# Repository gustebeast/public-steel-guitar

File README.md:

# Public Steel Guitar

A pedal steel guitar **you can build yourself, from parts anyone can buy.**

That is the whole point, and it is what the name means.

A pedal steel is a remarkable piece of engineering. The mechanical changer —
rods, bellcranks and pull-fingers moving a dozen strings through precise
intervals under hundreds of newtons, with a feel that generations of players
have refined — is one of the most sophisticated mechanisms in any instrument,
and the builders who make them are doing precision machining in small numbers,
by hand, at prices that reflect exactly that. It is skilled work and it is worth
what it costs.

It is also, by its nature, work that a player cannot do at home. That is the
constraint this project takes on: **not to make a better pedal steel, but to
make one that a person can source, build, modify and repair entirely
themselves.** Every printed part is in this repository as parametric source.
Every purchased part is a catalogue SKU with a supplier link in
[`BOM.md`](BOM.md), which comes to **~$1,060 per instrument** — approximate, and
several lines are still unverified — and the electronics are generated from
source too, so the boards can be re-fabbed by anyone rather than bought from us.
Motors dominate that total; there is one model, fully populated, with no
cut-down version. Nothing here needs a machine shop, a
proprietary part, or our involvement.

**Status:** CAD and electronics in progress; no physical prototype yet. The
mechanism is build-verified geometry (every commit is gated for part collisions,
swept collisions, wall thickness and unsupported overhangs), and **ten custom
PCBs are generated, routed and fab-packaged from source** — see `elec/`. What
does not exist yet is firmware: the copedent lives in a data table the 3D viewer
reads, and nothing commands a motor. [`docs/design-validation.md`](docs/design-validation.md)
tracks what the instrument can and cannot yet be shown to do, behaviour by
behaviour, including the open items. See
[`electromechanical-pedal-steel-spec.md`](electromechanical-pedal-steel-spec.md)
for the full design rationale and history.

**View it in 3D** (no install, no account):
<https://gustebeast.github.io/public-steel-guitar/> — an interactive model of the
instrument body, strings, nut block, and motor/changer drivetrain.

**License:** [CERN-OHL-S 2.0](LICENSE) (strongly reciprocal open hardware).

## Why it is built this way

Almost every design decision here follows from that one constraint. The
mechanism is not the goal; it is what is left once you insist that a person with
a 3D printer and a credit card can make the whole instrument. The column on the
left is not a criticism — it is the toolset a professional shop has and a player
usually does not.

| A shop can | So instead | Because |
|---|---|---|
| Mill a body from hardwood | **Printed PETG-GF and PCTG** | A printer is a machine people already own, and a file is not tooling. Changing a dimension is an edit, not a new setup. |
| Machine a changer: rods, bellcranks, pull-fingers, fitted as a set | **One commodity stepper and a GT2 belt per string** | Nothing in the drivetrain is made to order. A stepper, a belt, a trapezoidal screw and a nut are catalogue parts with several suppliers each. |
| Set the copedent in the pull-rod geometry | **The copedent is a data table** | Falls out of the above rather than being the aim: once each string has its own actuator, the mapping is software and costs nothing to change. |
| Keep spares and service what it built | **Every part is a file or a SKU** | Print the part again, or order the same screw — without depending on any one supplier staying in business. |
| Ream, tap, press and fit by hand | **One 2.5 mm hex key, heat-set inserts, no glue** | Fewest tools, one screw family, and every joint comes apart — so it can be repaired and modified, not just built. |

**What this gives up is real.** A mechanical steel needs no electricity, no
firmware and no motors; it will work in fifty years with a screwdriver, and its
feel is the product of decades of refinement by people who play them. This
instrument trades all of that for self-sufficiency. It is a different
instrument, not a cheaper copy of a good one — and if you want a pedal steel
rather than this, buy one from a builder.

## The concept, in one paragraph

So: each of the 10 strings terminates on the **nut of its own self-locking
leadscrew**, driven by a **closed-loop stepper** (MKS SERVO42D) through a
twisted GT2 belt. A traditional pedal steel changes pitch by pulling the
string's anchor with a mechanical changer, and which pedal pulls which string is
fixed in the hardware; giving every string its own stock actuator is the
cheapest way to get the same job done out of parts that already exist.
Pedals and levers are just **sensors**; firmware looks up the active copedent
and commands the relevant motors to new positions. Any pedal can bend any
combination of strings by any interval, changeable between songs. Because the
fine-pitch single-start screw is **non-back-drivable**, string tension cannot
move it: the motors are completely unpowered at rest — no holding current, no
heat, no idle noise — and the instrument holds its tuning even switched off.

## System concepts

Everything below is downstream of the buildability constraint: where there was a
choice between a clever part and an obtainable one, the obtainable one won.

- Per-string servo/stepper actuation of a pedal-steel changer, with a
  **software-reconfigurable copedent** (pedal/lever sensors → lookup →
  per-string position targets).
- **One bearing size, one screw family, one hex key.** A 688ZZ carries every
  axle; every fastener is an M4 button head on a 2.5 mm key; threads are
  heat-set brass inserts rather than tapped plastic. Fewer SKUs to source is
  the same goal as fewer tools to own.
- **No glue and no flex fittings anywhere.** Every joint is a screw, a slide or
  a captured pin, so any part can come out and be reprinted — which is what
  makes a repair a repair rather than a rebuild.
- A **self-locking (non-back-drivable) leadscrew per string** holding pitch
  with zero motor power, and serving as the tuning machine (no manual tuners).
- **Two nested control loops**: a fast feed-forward path (pedal position →
  copedent → motor position) with no pitch detection in the playing path, and
  a slow calibration loop using per-string pickup **pitch detection to correct
  the position→pitch map** (drift correction without touching the copedent).
- A **CAN-bus network of closed-loop actuators** (one node per string)
  commanded by a central controller reading pedal/lever angle sensors.
- The **vertical under-string actuator layout**: each string turns 90° over a
  per-string bridge bearing and runs down to a short vertical screw, motors
  lying flat under the speaking length in a staircase, driven by twisted
  belts — yielding a thin instrument (~100 mm).
- String termination is a **laser-cut steel nut plate** per string: its
  crown is the break, the string takes ONE wrap round a shared Ø8 rod, the
  plate's shelf pinches the one strand under the rod, and a side screw pins
  the tail to the plate. Both pinches are steel on steel, and the plate's
  crown-to-shelf height is a cut edge, so the strings level to the laser's
  accuracy rather than the printer's.
- **There is no printed carriage.** The leadscrew's own H-nut does both jobs:
  its +X ear anchors the string (ball end underneath, tension pulling it up
  against the ear, exactly a guitar bridge plate) and its -X ear rides the
  guide rod. That deleted a printed part ×10, twenty M2 screws and ten spacers.
- **Both ends of travel are hard stops on metal.** Up, the nut's flange lands on
  the changer room's ceiling (the restringing position). Down, the nut's boss
  lands on the thrust bearing's inner ring, so the reaction closes through the
  screw and loads nothing printed. Firmware soft limits are still wanted so a
  normal move never reaches either, and the guide rod's upper retention is
  deferred. See `docs/design-validation.md` B11.

## How the mechanism works

**The string's path** (from the player's left): each string's plain end runs
over the crown of its own **steel nut plate** (laser-cut 304, 4 mm) in the
**nut block** fused into the keyhead endplate, then takes **one** wrap round a
shared **Ø8 wrap rod**. An M4 height screw pushes the plate up until its shelf
pinches the one strand under the rod, which sets the string's height off the
string itself, and an M4 side screw in the keyhead's -X face pins the tail to
the plate. Until the plates arrive a printed stand-in with a Ø4 dowel for a
crown fits the same pocket. The speaking length (615 mm, ≈24.2″ scale) runs to the bridge, turns
90° over a **per-string 688ZZ bearing** on a Ø8 ground shaft (so the bend is
near-frictionless and tension equalizes across it), and drops vertically to the
**leadscrew's own nut**. The ball end sits under that nut's +X ear with the
string up through a Ø3 hole — tension pulls the ball against the ear, exactly a
guitar bridge plate — so restringing needs no tools at the moving end.

**The drive** (per string): `MKS SERVO42D closed-loop stepper (CAN) → GT2 belt
(twisted 90°, 1:1) → screw pulley → Tr8×2 vertical leadscrew (36.28 mm) → its
own H-nut → string`. **There is no printed carriage**: the nut's two mounting
ears do both jobs one did — the +X ear anchors the string, the -X ear rides a
**Ø2.5 hardened dowel pin** for anti-rotation. An axial thrust path (support
bearing + a second bearing up in the endplate slab) carries the string pull,
which is off-axis by 8 mm and therefore a standing ~956 N·mm couple.

The screw is what holds tune with the motors unpowered, and that is a friction
argument rather than a property of the part: mean Ø7, 2 mm lead, a **5.20° lead
angle**, so it is self-locking while μ ≥ 0.088 — comfortable dry or greased, and
**not** self-locking on a PTFE-loaded lubricant. Do not lubricate these screws.

Total travel is **8.35 mm**, budgeted as 4.00 mm of slack-to-pitch take-up when
the string goes on, 2.35 mm for four semitones of raise, and 2.00 mm of margin
for break-in. A semitone is about 0.5 mm at the modelled stretch — but the real
figure varies several-fold per string with gauge and construction, which is one
of the open items in `docs/design-validation.md`.

**The structure**: two deep I-beam side rails (3 printed segments joined by
sliding dovetails), per-motor cross-ribs, and a one-piece **bridge endplate**
that closes the box and carries the bridge-bearing axle on two arms plus a
nine-finger **support comb** (the Ø3 axle alone would bend under ~1.5 kN of
string wrap load; the comb cuts its free span to one string pitch *and* acts
as the assembly jig — drop the ten bearings into the comb slots and slide the
shaft through everything in one pass). Motors mount on faceplate walls with
round bolt holes, packed 1.6 mm apart — a screw-driven clamp on each belt
takes up the tension, so the motors never slide. Every printed part is self-supporting at
45° for a 0.8 mm nozzle. Materials (the build exports into per-material
folders): **PETG-GF** for every stiffness/creep-critical part — chassis,
both endplates, leg tubes — **PCTG** for compliant and
fine-feature parts and the whole deck (nothing snaps: no flex fitting anywhere
in the instrument, by design) — the panels print as two-filament
pairs (transparent-PCTG base whose fret lines run full-depth through the
plate + a colour-PCTG layer between them; no glass fiber on the forearm-rest
surface).

**Legs**: four quick-attach legs join the body at the corners with slide-in
octagon joinery and a cross-pin — no glue anywhere in the instrument, so every
part comes apart again. Each leg-to-leg junction is a cadkit octagon slide
joint retained by a single M4 (extraction only — the joinery takes the force),
so the instrument breaks down for transport in seconds. The legs must
print in pieces for build volume anyway, so the pieces double as the coarse
height adjustment: each stackable segment steps the height 142 mm, and a
clamped sliding shaft at the bottom spans 150 mm — more than one step — so
the bands overlap and **any** height from ~240 mm up is reachable (two
segments cover 525–675 mm; add or drop segments from there).

**Electronics** (firmware not in this repo — see `elec/` for the boards): a
**CH32V307** on the motor-controller board reads the control sensors and speaks
CAN to the ten servos, and a **Raspberry Pi 5** does everything else — audio,
UI, copedent. The split is a latency decision: the MCU runs only the
sensor→motor loop with saved offsets, so nothing in the playing path waits on
Linux. There is no Teensy and no ADC stack; the CH32V307 absorbed the first and
the optical pickup board the second. The two live in the keyhead bay, mounted
on cradles fused into the endplate rather than on a tray.

**Two CAN buses**, both classic at 500 kbps because the SERVO42D is
classic-only: **bus A** carries 24 V and CAN to the ten motors on their own
pigtails, fed from **both ends** of the trunk so the worst-loaded segment
carries about half the fleet. **Bus B** is a 5 V trunk-and-drop for the control
sensors, so unplugging a control never breaks the bus.

Panel I/O (1/4" TS line out, DC inlet, USB) is on the **output + panel board**
at the bridge end, which also carries the whole magnetic audio path: ADC, DAC,
USB hub, and a **true-bypass relay** — de-energized, the raw pickup runs
straight to the jack with no converters in the path; energized, the processed
output goes instead. The ADC is fed either way, so pitch detection always
works. The modeled harness is
color-coded per electrical net (spliced runs share a color; every unique
source→dest pairing differs) and routed through diamond raceways in the
cross-ribs; the overlap gate verifies the wires touch nothing but their own
endpoints. A **removable top deck** (PCTG panels riding grooves in the rail tops so they
can't fall off when inverted, yet pull out toward -X for motor service once the
keyhead endplate is off) covers the motors + electronics, carries printed
fret-position lines, doubles as a hand rest, and mounts the **UI station**: a
display and one Alps multi-control (rotary + 4-way + push) on their own routed
board, held by two deck spigots for X, Y and rotation with a single M4 for Z.

The bridge end of the deck is split into 20 mm slots. A **pickup-carrier piece**
holds the pickup as a tray: it pokes up through an opening and rests on three M4
leadscrew jacks standing on a **floor that runs under it** — turn them from
above to set the string gap, with the heads captured in the deck and the plate
riding the thread as a heat-set nut, for about 12 mm of travel. The pickup is
retained to the plate alone: a +Y wall it butts against, and a horizontal M4
grub pushing it into that wall, so the plate still travels. Coarse
bridge-to-neck position comes from re-slotting the piece; the plate slides ±17
on it for fine tone position. The remaining slots take **swappable filler
bands** — and they are now one part, not three: the bands carry no fret lines,
so any band fits any slot.

⚠ The deck's lighting is in flight: a body strip along the +Y rail, fret-marker
boards behind the deck panels, and a down-firing foot strip, all generated in
`elec/` and all of them newer than this paragraph.
The playing path is pure feed-forward — pedal moves map directly to motor
positions, so there is no pitch-tracking latency while playing. A per-string
pickup (e.g. a hex/multichannel pickup) feeds slow pitch detection used only
when calibrating: it measures each open string and corrects the
position→pitch map, absorbing drift from temperature, creep, or string aging.
The servos retune the instrument on demand; there are no manual tuning
machines anywhere.

## Building the CAD

CadQuery on Python 3.12 generates a STEP file per printed part, and the whole
assembly as the model the web viewer shows. The assembly places ~960 components: the printed parts, every
purchased-part dummy, the ten PCBs read back from their own routed geometry, and
the wiring harness drawn as real cable — every conductor, with its connectors.

```bash
py -3.12 -m src.build              # all parts + the viewer's model (the guaranteed full build)
py -3.12 -m src.build --part NAME  # one part, but still pays the ~26s module-level import
py -3.12 -m src.build --list       # list part names
py -3.12 -m src.build --geom       # belt-geometry report
py -3.12 -m tools.fast_build NAME  # ITERATION: rebuild one part in <1s-9s — imports ONLY that
                                   #   part's module, not all of src.build. Builds FRESH (no
                                   #   stale cache); handles 59/71 parts, falls back for the rest.
py -3.12 -m tools.check_overlaps   # design gate: any unintended interpenetration.
                                   #   A full build runs this gate ITSELF on the model it just
                                   #   made, so you rarely need it standalone. The scan is a few
                                   #   seconds (an incremental cache keyed on each part's
                                   #   geometry — only changed pairs are re-measured); standalone
                                   #   cost is dominated by rebuilding the model first.
                                   #   --no-gate opts out.
py -3.12 -m tools.check_sweep      # rotating parts swept through a full turn (the overlap
                                   #   gate is structurally blind to this)
py -3.12 -m tools.check_ceilings   # unsupported overhangs, per part, in its own print pose
py -3.12 -m tools.check_walls      # thin walls / minimum material
py -3.12 -m tools.check_beads      # dimensions on the nozzle-width grid
py -3.12 -m tools.check_cable_pairs # two cables sharing one lane -- the overlap gate treats
                                   #   wire-on-wire as an insulated crossing, so it cannot see it
py -3.12 -m tools.check_part_specs # the CAD's board dimensions against the ROUTED boards
py -3.12 -m tools.check_dead       # source drift: definitions nothing names any more
py -3.12 -m tools.build_profile    # per-part/module build-cost + face-count regression gate
py -3.12 -m tools.export_glb       # the web viewer's model and page alone (docs/)
```

- `src/dimensions.py` — the coordinate frame (+X along the strings toward the
  bridge, +Y across, +Z up) and **every** dimension as a named constant.
- `src/components.py` — schematic dummies of purchased parts (motor, screw,
  nut, bearings, pulleys, belt, strings, dowels) used only in the assembly.
- Printed parts, by area (`py -3.12 -m src.build --list` is the authoritative
  list — it is generated, this is a map):
  - **body**: `chassis_0/1/2` (each one file with its `_light` window body), `bridge_endplate`,
    `keyhead_endplate` (nut block fused in), `nut_slide_insert` (the nut plate's printed
    stand-in; the steel `nut_plate` is laser cut, `steel/nut_plate.step`)
  - **top deck**: `top_plate_*` segments, each one file with its colour inlay body,
    `pickup_zplate` (the pickup's height plate)
  - **drivetrain**: `screw_pulley_hi`/`_lo`, `motor_pulley`, `tension_fork`,
    and the belt-tension clamp (one `clamp_half` SKU fitted twice per string)
  - **controls**: `knee_housing`/`knee_lever`, `kv_housing`/`kv_lever`,
    `pedal_bar_a/b/c`, `pedal_lever`, and the shared feel cartridge
    (`cart_base`/`cart_piston`)
  - **UI**: `ui_clamp`, `ui_knob` — the deck's control station, a display and
    one Alps multi-control, clamped by plastic with a single M4 for Z only
  - **legs**: `fixed_sleeve`/`adjust_sleeve`, `fixed_tenon`/`adjust_tenon`,
    `body_adapter*`, `leg_foot` (TPU), and the latch set
  - **coupons**: `test_*` — print-fit test pieces, not part of the instrument
- Every gate exits non-zero on a finding, and `src.build` runs the overlap and
  sweep gates itself on the model it just built.

Envelope ≈ 100 × 200 × 655 mm (thick × across × long) — thin enough to sit on
a keyboard rig. 10 strings at 9.5 mm pitch at the bridge.

## The electronics

Ten boards, each generated from Python rather than drawn: schematic in
[skidl](https://github.com/devbisme/skidl), placement and autoroute driven from
the same source, then DRC and a fab package. The CAD reads every board back from
its own routed geometry (`elec/geom/*.geom.json`), so the plastic cannot drift
from the board it has to hold.

| Board | What it does |
|---|---|
| `optical` | per-string optical pickup + the analog front end; pitch detection for the calibration loop |
| `output_panel` | the front panel and the whole magnetic audio path — ADC, DAC, USB hub, true-bypass relay |
| `motor_ctrl` | CH32V307 + two CAN transceivers: the sensor→motor loop, and both buses' upstream end |
| `lever_sensor` | one per control — an MA730 reading a diametric magnet on the control's axle |
| `can_tee` | a bus junction so unplugging any device never breaks the trunk |
| `ui_board` | the deck's display + multi-control station |
| `fret_led_mid` / `fret_led_key` | fret-marker lighting, one board per deck panel |
| `foot_led` | down-firing foot lighting |

```bash
py -3.12 elec/finish.py elec/out/BOARD   # place, route, DRC and package one board
py -3.12 -m elec.audit_board BOARD       # the checks that outlive a DRC report
py -3.12 -m elec.cad_geom_check          # every board against the CAD that holds it
```

⚠ A `*-drc.rpt` in the repository root is **not** evidence — those files go stale
silently. `finish.py` and `audit_board.py` are the record.

## Repository layout

| Path | What |
|---|---|
| `src/` | CadQuery source — one module per printed part + helpers |
| `tools/` | the checkers (`check_*.py` — overlaps, sweep, ceilings, walls, beads, dead code), `fast_build` (fast single-part iteration), `build_profile` (build-cost/regression gate), the web-viewer exporters |
| `elec/` | the PCB sources — schematic + layout + autoroute + DRC + fab output, generated with skidl/KiCad, one module per board |
| `elec/geom/` | each routed board's measured geometry, committed — what the CAD reads so the plastic tracks the board |
| `cadkit/` | shared CAD library, vendored as a git subtree from its own repo and used by ten projects — edit it there, not here |
| `docs/` | GitHub Pages 3D viewer (`index.html` + `assembly.glb`), and the design notes below |
| `docs/design-validation.md` | what the instrument can and cannot yet be shown to do, behaviour by behaviour, with the open items |
| `INSTALL_NOTES.md` | installation steps the CAD can't show (thread lock, order, settings) — raw notes for the future install doc |
| `BOM.md` | purchased parts with sourcing links and prices |
| `electromechanical-pedal-steel-spec.md` | the full design specification and rationale |
| `*.step` | generated geometry (per part + full assembly) |

---

Copyright © 2026 gustebeast. Licensed under CERN-OHL-S 2.0 — you may build,
modify, and sell hardware from these sources, but modified sources must remain
available under the same license.

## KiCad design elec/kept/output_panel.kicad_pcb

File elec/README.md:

# `elec/` — the instrument's six PCBs, from source to a JLCPCB order

Everything here is **generated**. No board was drawn in a GUI, and none should be:
the point is that changing a parameter — the string spacing, the number of strings,
a connector — and re-running produces a new, orderable board with no one having to
open a layout editor and nudge things.

If you are reading this because you want to change something, read
**"What to change, and what regenerates itself"** at the bottom first.

## The boards

| board | what it is | qty |
|---|---|---|
| `can_tee` | CAN trunk junction, one per motor | 11 |
| `lever_sensor` | MA730 angle sensor on a pedal/knee lever | 8 |
| `motor_ctrl` | CH32V307 + dual CAN + the 24→5 V supply | 1 |
| `output_panel` | the front panel, both audio conversions, a USB hub | 1 |
| `optical` | 10-string optical pickup: 20 photodiodes, 20 TIAs, USB HS | 1 |
| `fret_led_mid` | frets 24–10: 15 RGBW zones, 60 LEDs, 5× TLC59711 | 1 |
| `fret_led_key` | frets 9–1: 9 RGBW zones, 36 LEDs, 3× TLC59711 | 1 |

⚠ **`fret_led_*` is the SECOND board whose geometry is an INPUT rather than an output**
(the first is `optical`). One module, `fret_led.py`, cuts to two panels; every fret X, the
four LED Y positions, the board width and the Z stack come from `src/fret_light.py`. It
also carries two checks the rest of the directory does not need -- `check_placement`
(courtyards, read out of the footprint files) and `check_walls` (the DECK hangs a 1.6 mm
light-cell wall onto this board's top face at every fret boundary, and no DRC can see it).
Both run before the netlist is written.

## Two Pythons, and it is not optional

* `py -3.12` runs the **board modules** (`elec/<board>.py`). They need `skidl` and,
  for the boards whose geometry is an input, `cadquery`.

  ⚠ **NOT `fab.py`, whatever this line used to say.** `fab.py` imports `pcbnew`
  inside `_check_drill` -- the check that compares the drill file against the board's
  own holes and REFUSES rather than reports -- so under 3.12 it dies with
  `ModuleNotFoundError: pcbnew` after writing the gerbers. Run it under KiCad's Python
  like the other three stages (found 2026-09-30, packaging the fret LED boards).
* KiCad's own Python (`C:\Program Files\KiCad\10.0\bin\python.exe`) runs
  `layout.py`, `route.py` and `verify.py`, because those need `pcbnew`, which ships
  only inside the KiCad install and cannot be pip-installed.

They share nothing but files. A board module writes `<board>.net` and
`<board>.board.json`; everything downstream reads that pair. **This is why
`layout.py` can never `import src/`** — KiCad's Python has no cadquery.

## Running it

```bash
py -3.12 elec/optical.py                      # -> out/optical.{net,board.json}
```

```bash
cd elec/out && "C:/Program Files/KiCad/10.0/bin/python.exe" ../layout.py optical
```

```bash
cd elec/out && "C:/Program Files/KiCad/10.0/bin/python.exe" ../route.py optical
```

```bash
cd elec/out && "C:/Program Files/KiCad/10.0/bin/python.exe" ../fab.py
```

`fab.py` does the last three checks itself and **refuses to package a board that
fails any of them**: DRC, "is this actually routed", and `verify.py`'s declared
high-speed budgets. It writes `out/fab/<board>.zip` — gerbers, a merged Excellon
drill, and JLCPCB-column BOM and CPL.

`elec/out/` is **not** under version control. Everything in it is a build artifact
and is meant to be reproducible from the board modules; the routed `.kicad_pcb`
especially, because freerouting is non-deterministic and two runs differ.

## What each stage owns

**`<board>.py`** — the design. Parts, nets, footprints, and where each part goes.
For five boards the outline is an *output* of the part list. The optical board is
the exception: its geometry is dictated by the instrument, so it **imports its
placements from `src/optical_pickup.py`** and asserts the two agree part-for-part.

**`layout.py`** — netlist + placement → `.kicad_pcb`. Also does the things a router
should not be asked to do:
* pours the zones (and **builds the connectivity graph first** — without it the
  filler discards every island and a pour silently fills to zero area),
* gives every pad on a plane net **its own via down to the plane**, so a ground
  connection does not depend on pour islands the router will later fragment,
* drops single-pad nets, which cannot be routed and only bloat the search space,
* moves silkscreen to `F.Fab` for parts whose outlines collide by design.

**`route.py`** — Specctra DSN → freerouting → SES → board. Declares `plane_layers`
to the router as `(type power)` so it **stops routing through the ground plane**,
clamps any track it necks below the fab floor, and refills the pours afterwards.

**`verify.py`** — what DRC cannot answer. DRC says "manufacturable"; this says
"correct": matched-length groups, differential pairs staying on the same layers,
via budgets on high-speed nets. Budgets live in `board.json` and each carries a
`why`, because a limit with no stated basis is one someone later relaxes.

**`fab.py`** — the handoff, plus the sourcing gate. A part value that is neither
sourced, nor a generic passive, nor **declared open** fails the build. That exists
because nothing else in the pipeline reads the `value` field, so a stale part number
is invisible right up until the wrong parts arrive.

## What to change, and what regenerates itself

**Change the board module.** Everything downstream follows. In particular:

* **String spacing / count** — change `src/dimensions.py`, then re-run
  `elec/optical.py`. The sensor row, the board outline, the deck-band assertions and
  the conduit clearance are all derived; they will either follow or **fail loudly**.
  A failing assertion here is the system working, not breaking: it means the new
  spacing broke a constraint someone wrote down, and the message says which.
* **A connector or a part** — edit the board module. `fab.py` will stop until the new
  value is sourced or declared.
* **Anything in `elec/out/`** — don't. It is regenerated.

## Known limits — read these before trusting a regenerated board

1. **Freerouting is non-deterministic and does not always converge.** The optical
   board (153 parts) lands around 20 unconnected of ~380; the other five reach zero.
   Pass count is *optimiser* passes: the curve is flat past about 10, and high counts
   can exceed the timeout and produce **no** result. `route.py` now says so rather
   than leaving a board that looks like it failed to connect.
2. **The optical board's twenty summing nodes are routed by the autorouter**, so the
   most performance-critical geometry on the instrument differs between runs and is
   invisible to DRC. Pre-routing them was attempted and abandoned — see the note in
   `optical.py`. If analog performance disappoints, start there.
3. **Rotations are not verified.** The CPL carries KiCad's convention; JLCPCB's
   placement machine wants the LCSC part's, and they differ per part. Check every
   rotation in JLCPCB's previewer before paying. This is the one step that is still
   genuinely manual, and it is a *review* step, not a design one.
4. **Sourcing is open on several parts** — `fab.py` lists them. Two are blocking:
   the USB3343 PHY was out of stock at LCSC, and the STM32H743ZIT6 stock was thin.

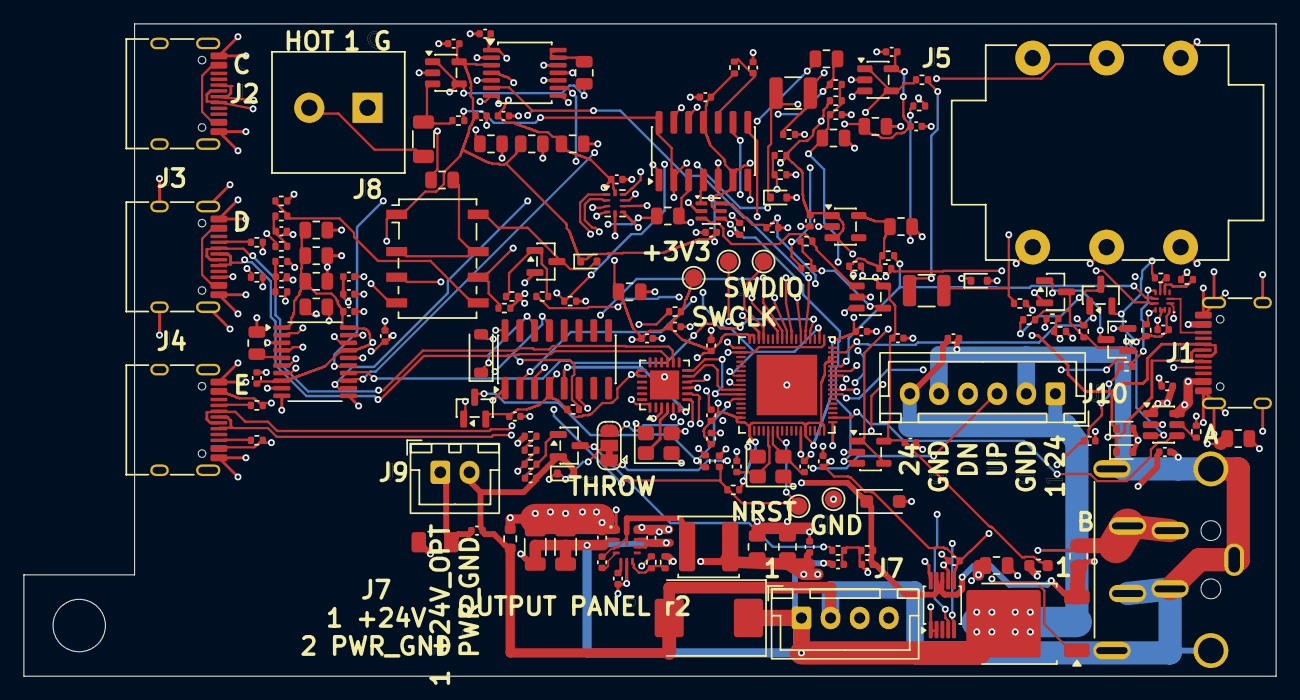
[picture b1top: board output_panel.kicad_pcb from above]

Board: 4 copper layers, 107.5 x 56.0 mm, 179 parts (0 on the bottom side), 112 nets.

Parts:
C1, C41: 2.2uF/100V; C_1210_3225Metric
C2, C17: 10uF/50V; C_1206_3216Metric
C3, C4, C18, C55, C56, C61, C65: 100nF/50V; C_0402_1005Metric
C5, C6, C64: 22uF/16V; C_0805_2012Metric
C7, C9, C20, C21, C23, C25, C27, C29, C36, C38, C40: 10uF; C_0805_2012Metric
C8, C10, C11, C12, C13, C14, C19, C22, C26, C28, C30, C43, C44, C46, C47, C50, C51, C52, C53, C54, C57, C59, C60, C62, C66, C67, C68, C70, C71: 100nF; C_0402_1005Metric
C15, C16: 15pF; C_0402_1005Metric
C24, C39, C42: 1uF; C_0805_2012Metric
C31: 10uF; C_0402_1005Metric
C32, C33: 2.2uF; C_0805_2012Metric
C34, C45: 2.2nF C0G; C_0402_1005Metric
C35, C58: 1uF; C_0402_1005Metric
C37: 100nF C0G; C_1206_3216Metric
C48, C63: 1uF/25V; C_0402_1005Metric
C49: 22nF/50V; C_0402_1005Metric
C69: 10uF/16V; C_0805_2012Metric
D2, D3: LESD5L5.0CT1G; D_SOD-523
D4: 1N4148WT; D_SOD-523
D5, D7: ESD5B5.0ST1G; D_SOD-523
D6: SMCJ24A; D_SMC
D8: BZT52C10T-7; D_SOD-523
D9: DSS16; D_SOD-123
D10: SMF24A; D_SOD-123F
F1: JFC1206-1100FS; Fuse_1206_3216Metric
FB1: BLM18KG601SN1D; L_0603_1608Metric
J1, J2, J3, J4: TYPE-C-31-M-12; USB_C_Receptacle_HRO_TYPE-C-31-M-12
J5: NMJ6HCD2; Jack_6.35mm_Neutrik_NMJ6HCD2_Horizontal
J6: KPJX-4S-S; Kycon_KPJX-4S-S
J7: B4B-XH-A; JST_XH_B4B-XH-A_1x04_P2.50mm_Vertical
J8: MX128-5.0-02P-Y; MaiXu_MX128-5.0-02P_1x02_P5.00mm
J9: B2B-XH-A; JST_XH_B2B-XH-A_1x02_P2.50mm_Vertical
J10: B6B-XH-A; JST_XH_B6B-XH-A_1x06_P2.50mm_Vertical
JP1: THROW; SolderJumper-3_P1.3mm_Bridged12_RoundedPad1.0x1.5mm
K1: G6K-2F-Y-DC5; Relay_DPDT_Omron_G6K-2F-Y
L1: SWPA5040S4R7MT; L_Sunlord_SWPA5040S
Q1: AO3400A; SOT-23
Q2: SQD50P06-15L; TO-252-2
Q3, Q5, Q6: 2N7002; SOT-23
Q4, Q7: AO3401A; SOT-23
R3, R4: 5k1; R_0402_1005Metric
R5: 100R; R_0402_1005Metric
R6, R7, R14, R15, R19, R24, R25, R28, R35, R42: 10k; R_0402_1005Metric
R8, R47: 1M; R_0402_1005Metric
R9, R20: 220R; R_0402_1005Metric
R10, R11, R16, R17, R18, R21, R22, R36, R37, R38, R39, R44, R46, R52: 100k; R_0402_1005Metric
R12: 24k9 1%; R_0402_1005Metric
R13, R23: 470R; R_0402_1005Metric
R26, R27: 10k 0.1%; R_0402_1005Metric
R29, R30: 56k; R_0402_1005Metric
R31: 330k; R_0402_1005Metric
R32, R40: 150k; R_0402_1005Metric
R33, R34, R43, R48, R49, R50, R51: 4k7; R_0402_1005Metric
R41: 910k; R_0402_1005Metric
R45: 15k 1%; R_0402_1005Metric
R54: 1k; R_0402_1005Metric
R60: 0R; R_0603_1608Metric
R61: 5mR 1W; R_0805_2012Metric
TP1, TP2, TP3, TP4, TP5: SWD; TestPoint_Pad_D1.5mm
U1: CH32V307WCU6; QFN-68-1EP_8x8mm_P0.4mm_EP5.2x5.2mm
U2: PCM1808PWR; TSSOP-14_4.4x5mm_P0.65mm
U3: PCM5102APWR; TSSOP-20_4.4x6.5mm_P0.65mm
U4: CH334F; HVQFN-24-1EP_4x4mm_P0.5mm_EP2.5x2.5mm
U5: LMR33630BRNXR; Texas_RNX0012_VQFN-HR-12_2x3mm_P0.5mm
U6: AP2112K-3.3TRG1; SOT-23-5
U7, U8, U9, U11: TLV9061IDBVR; SOT-23-5
U10: AD8402ARZ10; SOIC-14_3.9x8.7mm_P1.27mm
U12: TS5A3159DCKR; SOT-363_SC-70-6
U13: TUSB320LAIRWBR; Texas_RWB0012A_X2QFN-12_1.6x1.6mm_P0.4mm
U14: TS3USB221RSER; Texas_UQFN-10_1.5x2mm_P0.5mm
U15: TPS2553DBVR; SOT-23-6
U16: INA226AIDGSR; MSOP-10_3x3mm_P0.5mm_Tight
U17: CH340C; SOIC-16_3.9x9.9mm_P1.27mm
Y1: TAXM8M4RFDCET2T; Crystal_SMD_3225-4Pin_3.2x2.5mm
Y2: TAXM12M4RFBCCT2T; Crystal_SMD_3225-4Pin_3.2x2.5mm

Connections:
+3V3: C9.1, C10.1, C11.1, C12.1, C14.1, C22.1, C23.1, C25.1, C26.1, C27.1, C28.1, C29.1, C35.1, C36.1, C51.1, C52.1, C53.1, C66.1, C67.1, C68.1, C70.1, Q4.2, Q7.2, R6.2, R19.2, R42.1, R43.1, R48.1, R49.1, R50.1, R51.1, R52.1, TP5.1, U1.1, U1.13, U1.17, U1.31, U1.32, U1.50, U1.51, U1.67, U1.68, U2.4, U3.1, U3.8, U3.17, U3.20, U4.19, U4.20, U6.5, U13.12, U14.10, U16.6, U17.4, U17.16
+5V: C7.1, C8.1, C13.1, C21.1, C43.1, C44.1, C46.1, C47.1, C57.1, C58.1, C59.1, C60.1, D4.1, FB1.2, J4.A4, J4.A9, J4.B4, J4.B9, K1.1, R17.1, R29.2, R30.2, R38.1, R39.2, U2.3, U6.1, U6.3, U7.5, U8.5, U9.5, U10.6, U10.11, U11.5, U12.5
+24V: C2.1, C3.1, C17.1, C18.1, C49.2, C56.1, D6.1, F1.1, J7.1, J10.1, J10.6, Q2.2, U5.2, U5.9, U5.10
+24V_IN: C48.1, C55.1, D10.1, Q2.3, R32.1, R33.1, R61.2, U16.8, U16.9
+24V_JACK: J6.2, J6.4, R61.1, U16.10
+24V_OPT: C61.1, F1.2, J9.1
ADC_IN: C24.2, U2.13, U2.14
ADC_VREF: C19.1, C20.1, U2.1
AUDIO_PROC: R13.1, U3.6
AUDIO_SEL: C39.1, K1.3, R15.1
BOOT: C4.1, U5.4
BOOT0: Q7.3, R7.1, U1.63
BUCK_VCC: C63.1, U5.5
BUF_OUT: R9.1, R26.1, U7.1, U7.4
CC1: J1.A5, U13.1
CC2: J1.B5, U13.2
DAC_ATT: K1.4, R14.2
DAC_CAPM: C32.2, U3.4
DAC_CAPP: C32.1, U3.2
DAC_FILT: C34.1, R13.2, R14.1
DAC_LDOO: C30.1, C31.1, U3.18
DAC_OUT_R: R23.1, U3.7
DAC_R_FILT: C45.1, R23.2, R24.1
DAC_VNEG: C33.1, U3.5
DIRECT_AC: C38.2, K1.2, K1.7
FB: R11.2, R12.1, U5.7
FLASH_DTR_N: Q7.1, R52.2, U17.13
FLASH_RTS_N: D9.1, U17.14
FLASH_RX: U1.44, U17.3
FLASH_TX: U1.45, U17.2
GND: C2.2, C3.2, C5.2, C6.2, C7.2, C8.2, C9.2, C10.2, C11.2, C12.2, C13.2, C14.2, C15.2, C16.2, C17.2, C18.2, C19.2, C20.2, C21.2, C22.2, C23.2, C25.2, C26.2, C27.2, C28.2, C29.2, C30.2, C31.2, C33.2, C34.2, C35.2, C36.2, C40.2, C43.2, C44.2, C45.2, C46.2, C47.2, C51.2, C52.2, C53.2, C54.2, C57.2, C58.2, C59.2, C60.2, C62.2, C63.2, C64.2, C65.2, C66.2, C67.2, C68.2, C69.2, C70.2, C71.2, D2.2, D3.2, D5.2, D7.2, D10.2, J1.A1, J1.A12, J1.B1, J1.B12, J1.SH, J2.A1, J2.A12, J2.B1, J2.B12, J2.SH, J3.A1, J3.A12, J3.B1, J3.B12, J3.SH, J4.A1, J4.A12, J4.B1, J4.B12, J4.SH, J5.RN, J5.S, J5.SN, J5.TN, J8.1, Q1.2, Q5.2, Q6.2, R3.2, R4.2, R7.2, R10.2, R12.2, R15.2, R18.2, R21.2, R25.2, R28.2, R36.2, R37.2, R40.2, R44.2, R45.2, R47.2, R60.2, TP4.1, U1.12, U1.18, U1.49, U1.69, U2.2, U2.5, U2.10, U2.11, U2.12, U3.3, U3.9, U3.10, U3.11, U3.16, U3.19, U4.25, U5.1, U5.6, U5.11, U6.2, U7.2, U8.2, U9.2, U10.1, U10.5, U11.2, U12.2, U13.10, U13.11, U14.5, U14.6, U15.2, U16.1, U16.2, U16.7, U17.1, Y1.2, Y1.4, Y2.2, Y2.4
HUB_DN1_DM: U1.61, U4.11
HUB_DN1_DP: U1.62, U4.12
HUB_DN2_DM: J4.A7, J4.B7, U4.7
HUB_DN2_DP: J4.A6, J4.B6, U4.8
HUB_DN3_DM: U4.9, U14.1
HUB_DN3_DP: U4.10, U14.2
HUB_DN4_DM: U4.5, U17.6
HUB_DN4_DP: U4.6, U17.5
HUB_OVCUR_N: R19.1, U4.1
HUB_UP_DM: J3.A7, J3.B7, U4.14
HUB_UP_DP: J3.A6, J3.B6, U4.15
HUB_XI: U4.4, Y2.1
HUB_XO: U4.3, Y2.3
I2C2_SCL: R50.2, U1.29, U13.8, U16.5
I2C2_SDA: R51.2, U1.30, U13.7, U16.4
I2S_CK: U1.36, U1.58, U2.8, U3.13
I2S_MCK: U1.39, U2.6, U3.12
I2S_SDI: U1.60, U2.9
I2S_SDO: U1.38, U3.14
I2S_WS: U1.35, U1.53, U2.7, U3.15
INV_IN_N: R26.2, R27.1, U11.4
INV_OUT: R27.2, U11.1, U12.3
J1_VBUS: C69.1, J1.A4, J1.A9, J1.B4, J1.B9, R41.1, R46.1, U15.6
JACK_MODE: R37.1, U1.28, U12.6
JACK_RING: C41.2, J5.R, R21.1
JACK_TIP: C1.2, J5.T, R10.1
unnamed: J4.A5, R29.1
unnamed: J4.B5, R30.1
unnamed: J3.A5, R3.1
unnamed: J3.B5, R4.1
unnamed: Q1.1, R5.2, R36.1
unnamed: R42.2, U13.5
unnamed: R45.1, U15.5
unnamed: Q4.3, R54.1
NRST: C54.1, D9.2, R6.1, TP3.1, U1.7
OSC_IN: C15.1, U1.5, Y1.1
OSC_OUT: C16.1, U1.6, Y1.3
OUT_BLOCKED: C1.1, D5.1, R9.2
OUT_BUF_IN: C39.2, R16.1, U10.13
PICKUP_BUF: C24.1, C38.1, U8.1, U8.4
PICKUP_HOT: C37.1, J8.2
PICKUP_IN: C37.2, R8.1, U8.3
PI_DM: J2.A7, J2.B7, U14.3
PI_DP: J2.A6, J2.B6, U14.4
PORT_EN: Q5.3, Q6.1, R44.1, R54.2, U15.3
PORT_FAULT_N: R48.2, U1.19, U15.4
PORT_SEEN: Q5.1, Q6.3, R46.2, R47.1
POT_CS: R39.1, R40.1, U1.40, U10.7
POT_RS: C62.1, R38.2, U10.10
POT_SCK: U1.43, U10.9
POT_SDI: U1.42, U10.8
PWR_GATE: C48.2, C49.1, Q2.1, R31.1, R32.2
PWR_GND: C50.2, C55.2, C56.2, C61.2, D6.2, D8.2, J6.1, J6.3, J6.SH, J7.2, J9.2, J10.2, J10.5, Q3.2, R60.1
PWR_PULL: Q3.3, R31.2
PWR_SW_DN: J10.4, JP1.3
PWR_SW_UP: J10.3, JP1.1
RELAY: R5.1, U1.25
RELAY_COIL: D4.2, K1.8, Q1.3
RING_ATT: K1.5, R24.2, R25.1
RING_BLOCKED: C41.1, D7.1, R20.2
RING_BUF_IN: C42.2, R22.1, U10.3
RING_BUF_OUT: R20.1, U9.1, U9.4
RING_BUF_SEL: U9.3, U12.4
RING_GAIN: U10.4, U12.1
RING_SEL: C42.1, K1.6, R28.1
ROLE_ID_N: Q4.1, R43.2, U1.33, U13.9, U14.9
ROLE_INT_N: R49.2, U1.24, U13.6
ROLE_VDET: R41.2, U13.4
SW: C4.2, L1.1, U5.3, U5.12
SWCLK: TP2.1, U1.52
SWDIO: TP1.1, U1.48
SW_GATE: C50.1, Q3.1, R35.2
SW_PU_MID: R33.2, R34.1
SW_SENSE: D8.1, JP1.2, R34.2, R35.1
THRU_DM: D3.1, J1.A7, J1.B7, U14.8
THRU_DP: D2.1, J1.A6, J1.B6, U14.7
TIP_GAIN: U7.3, U10.12
V5_PRE: C5.1, C6.1, C64.1, C65.1, C71.1, FB1.1, L1.2, R11.1, U15.1
VBUS_PI_NC: J2.A4, J2.A9, J2.B4, J2.B9
VBUS_UP_NC: J3.A4, J3.A9, J3.B4, J3.B9
VMID: C40.1, R8.2, R16.2, R17.2, R18.1, R22.2, U10.2, U10.14, U11.3

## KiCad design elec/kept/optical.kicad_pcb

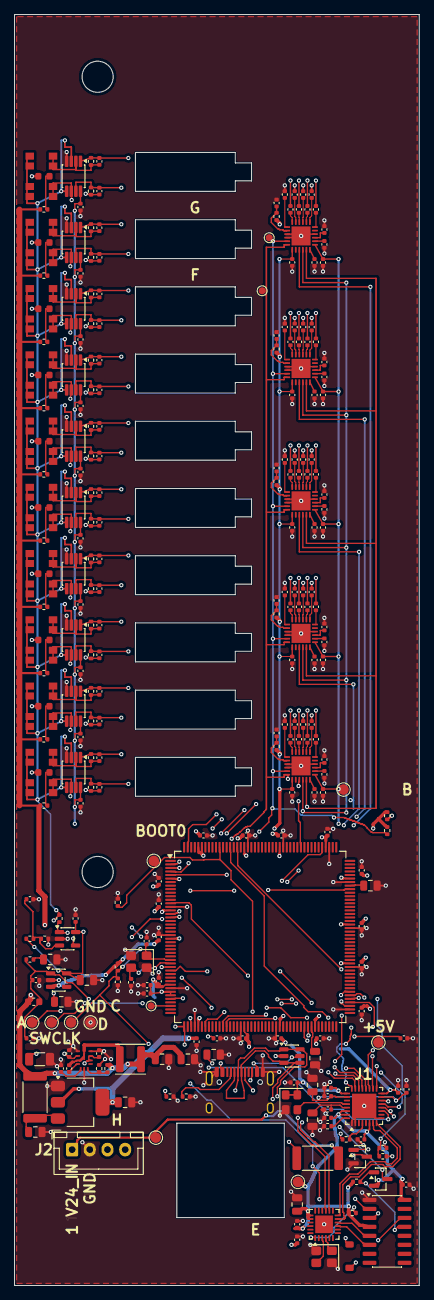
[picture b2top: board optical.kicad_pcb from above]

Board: 4 copper layers, 57.2 x 179.7 mm, 287 parts (0 on the bottom side), 180 nets.

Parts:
C100, C101, C102, C103, C104, C105, C106, C107, C108, C109, C110, C115, C116, C117, C118, C119, C121, C125, C128, C129, C135, C136, C137, C138, C139, C141, C142, C143, C144, C145, C163, C180, C183: 100nF; C_0402_1005Metric
C111, C114, C140, C166, C182: 1uF; C_0402_1005Metric
C112, C113, C130: 2.2uF; C_0805_2012Metric
C120, C122: 4.7uF; C_0805_2012Metric
C123, C124: 12pF; C_0402_1005Metric
C131, C132, C133, C134, C181: 10uF; C_0805_2012Metric
C160: 10uF/50V; C_1206_3216Metric
C161, C165: 100nF/50V; C_0402_1005Metric
C162, C167: 22uF/16V; C_0805_2012Metric
C164: 10uF/16V; C_0805_2012Metric
Cd1, Cd2, Cd3, Cd4, Cd5, Cd6, Cd7, Cd8, Cd9, Cd10: 100nF; C_0402_1005Metric
Cf1A, Cf1B, Cf2A, Cf2B, Cf3A, Cf3B, Cf4A, Cf4B, Cf5A, Cf5B, Cf6A, Cf6B, Cf7A, Cf7B, Cf8A, Cf8B, Cf9A, Cf9B, Cf10A, Cf10B: 2.2pF; C_0402_1005Metric
Ci11, Ci12, Ci13, Ci14, Ci21, Ci22, Ci23, Ci24, Ci31, Ci32, Ci33, Ci34, Ci41, Ci42, Ci43, Ci44, Ci51, Ci52, Ci53, Ci54: 10nF C0G; C_0402_1005Metric
Cm11, Cm12, Cm13, Cm14, Cm21, Cm22, Cm23, Cm24, Cm31, Cm32, Cm33, Cm34, Cm41, Cm42, Cm43, Cm44, Cm51, Cm52, Cm53, Cm54: 10nF C0G; C_0402_1005Metric
Cs11, Cs15, Cs19, Cs21, Cs25, Cs29, Cs31, Cs35, Cs39, Cs41, Cs45, Cs49, Cs51, Cs55, Cs59: 1uF; C_0402_1005Metric
Cs13, Cs16, Cs18, Cs23, Cs26, Cs28, Cs33, Cs36, Cs38, Cs43, Cs46, Cs48, Cs53, Cs56, Cs58: 10uF; C_0402_1005Metric
D1, D2, D3, D4, D5, D6, D7, D8, D9, D10: LTE-C9901; LED_0603_1608Metric
D11: DSS16; D_SOD-123
FB1: BLM18KG601SN1D; L_0603_1608Metric
J1: TYPE-C-31-M-12; USB_C_Receptacle_HRO_TYPE-C-31-M-12
J2: B4B-XH-A; JST_XH_B4B-XH-A_1x04_P2.50mm_Vertical
L1: WPN4020H4R7MT; L_Sunlord_SWPA4030S
PD1A, PD1B, PD2A, PD2B, PD3A, PD3B, PD4A, PD4B, PD5A, PD5B, PD6A, PD6B, PD7A, PD7B, PD8A, PD8B, PD9A, PD9B, PD10A, PD10B: PD15-22B/TR8; Everlight_PD15-22B
Q1: AO3400A; SOT-23
Q2: AO3401A; SOT-23
R1, R2, R3, R4, R5, R6, R7, R8, R9, R10: 180R 100mW; R_0402_1005Metric
R30, R31, R39, R52: 10k; R_0402_1005Metric
R32, R33: 5k1; R_0402_1005Metric
R34: 9k09 1%; R_0402_1005Metric
R35: 1k 1%; R_0402_1005Metric
R36, R42: 100R; R_0402_1005Metric
R37: 12k 1%; R_0402_1005Metric
R38, R53: 100k; R_0402_1005Metric
R40: 100k 1%; R_0402_1005Metric
R41: 24k9 1%; R_0402_1005Metric
R43: 1R; R_0402_1005Metric
R44: RK73B3ATTE2R0J; R_2512_6332Metric
R50, R51: 4k7; R_0402_1005Metric
R54: FRC2512F1R20TS; R_2512_6332Metric
Rf1A, Rf1B, Rf2A, Rf2B, Rf3A, Rf3B, Rf4A, Rf4B, Rf5A, Rf5B, Rf6A, Rf6B, Rf7A, Rf7B, Rf8A, Rf8B, Rf9A, Rf9B, Rf10A, Rf10B: 249k 1%; R_0402_1005Metric
Rs11, Rs21, Rs31, Rs41, Rs51: 10k; R_0402_1005Metric
TP1, TP2, TP3, TP4, TP5: SWD; TestPoint_Pad_D1.5mm
TP6, TP7, TP12: BRINGUP; TestPoint_Pad_D1.0mm
TP8, TP9, TP10, TP11: BRINGUP; TestPoint_Pad_D1.5mm
U6: STM32H743IIT6; LQFP-176_24x24mm_P0.5mm
U7: USB3300-EZK-TR; QFN-32-1EP_5x5mm_P0.5mm_EP3.45x3.45mm
U8: AP2114H-3.3TRG1; SOT-223-3_TabPin2
U9: TPS7A2033PDBVR; SOT-23-5
U10: USBLC6-2SC6; SOT-23-6
U11: TLV9061IDBVR; SOT-23-5
U13: LMR33630BRNXR; Texas_RNX0012_VQFN-HR-12_2x3mm_P0.5mm
U14, U15, U16, U17, U18: TLV320ADC3140IRTWT; Texas_RTW_WQFN-24-1EP_4x4mm_P0.5mm_EP2.7x2.7mm
U21, U22, U23, U24, U25, U26, U27, U28, U29, U30: TLV9062IDGKR; VSSOP-8_3x3mm_P0.65mm
U31: CH334F; HVQFN-24-1EP_4x4mm_P0.5mm_EP2.5x2.5mm
U32: CH340C; SOIC-16_3.9x9.9mm_P1.27mm
Y1: TAXM25M4RDBCCT2T; Crystal_SMD_3225-4Pin_3.2x2.5mm
Y2: CJO05-240003320B30; Oscillator_SMD_Abracon_ASE-4Pin_3.2x2.5mm
Y3: TAXM12M4RFBCCT2T; Crystal_SMD_3225-4Pin_3.2x2.5mm

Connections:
+3V3A: C110.1, C111.1, C132.1, C144.1, Cd1.1, Cd2.1, Cd3.1, Cd4.1, Cd5.1, Cd6.1, Cd7.1, Cd8.1, Cd9.1, Cd10.1, Cs11.1, Cs21.1, Cs31.1, Cs41.1, Cs51.1, R34.1, TP11.1, U6.38, U6.39, U9.5, U11.5, U14.1, U15.1, U16.1, U17.1, U18.1, U21.8, U22.8, U23.8, U24.8, U25.8, U26.8, U27.8, U28.8, U29.8, U30.8
+3V3D: C100.1, C101.1, C102.1, C103.1, C104.1, C105.1, C106.1, C107.1, C108.1, C109.1, C115.1, C116.1, C117.1, C118.1, C119.1, C121.1, C125.1, C128.1, C129.1, C131.1, C138.1, C139.1, C180.1, C181.1, C182.1, C183.1, Cs18.1, Cs28.1, Cs38.1, Cs48.1, Cs58.1, Q2.2, R31.2, R50.2, R51.2, R52.1, R53.1, Rs11.2, Rs21.2, Rs31.2, Rs41.2, Rs51.2, TP5.1, U6.6, U6.15, U6.23, U6.36, U6.49, U6.62, U6.72, U6.82, U6.91, U6.103, U6.114, U6.127, U6.136, U6.149, U6.159, U6.171, U6.172, U7.6, U7.16, U7.25, U7.30, U7.31, U8.2, U9.3, U14.19, U15.19, U16.19, U17.19, U18.19, U31.19, U31.20, U32.4, U32.16, Y2.1, Y2.4
+5V: C140.1, C141.1, C142.1, C143.1, FB1.2, R43.1, TP10.1, U9.1
+24V: C160.1, C161.1, C165.1, R44.2, U13.2, U13.9, U13.10
ADC1_AREG: Cs13.1, U14.2
ADC1_DREG: Cs16.1, U14.24
ADC1_IN1M: Cm11.1, U14.7
ADC1_IN1P: Ci11.2, U14.6
ADC1_IN2M: Cm12.1, U14.9
ADC1_IN2P: Ci12.2, U14.8
ADC1_IN3M: Cm13.1, U14.11
ADC1_IN3P: Ci13.2, U14.10
ADC1_IN4M: Cm14.1, U14.13
ADC1_IN4P: Ci14.2, U14.12
ADC1_VREF: Cs15.1, U14.3
ADC2_AREG: Cs23.1, U15.2
ADC2_DREG: Cs26.1, U15.24
ADC2_IN1M: Cm21.1, U15.7
ADC2_IN1P: Ci21.2, U15.6
ADC2_IN2M: Cm22.1, U15.9
ADC2_IN2P: Ci22.2, U15.8
ADC2_IN3M: Cm23.1, U15.11
ADC2_IN3P: Ci23.2, U15.10
ADC2_IN4M: Cm24.1, U15.13
ADC2_IN4P: Ci24.2, U15.12
ADC2_VREF: Cs25.1, U15.3
ADC3_AREG: Cs33.1, U16.2
ADC3_DREG: Cs36.1, U16.24
ADC3_IN1M: Cm31.1, U16.7
ADC3_IN1P: Ci31.2, U16.6
ADC3_IN2M: Cm32.1, U16.9
ADC3_IN2P: Ci32.2, U16.8
ADC3_IN3M: Cm33.1, U16.11
ADC3_IN3P: Ci33.2, U16.10
ADC3_IN4M: Cm34.1, U16.13
ADC3_IN4P: Ci34.2, U16.12
ADC3_VREF: Cs35.1, U16.3
ADC4_AREG: Cs43.1, U17.2
ADC4_DREG: Cs46.1, U17.24
ADC4_IN1M: Cm41.1, U17.7
ADC4_IN1P: Ci41.2, U17.6
ADC4_IN2M: Cm42.1, U17.9
ADC4_IN2P: Ci42.2, U17.8
ADC4_IN3M: Cm43.1, U17.11
ADC4_IN3P: Ci43.2, U17.10
ADC4_IN4M: Cm44.1, U17.13
ADC4_IN4P: Ci44.2, U17.12
ADC4_VREF: Cs45.1, U17.3
ADC5_AREG: Cs53.1, U18.2
ADC5_DREG: Cs56.1, U18.24
ADC5_IN1M: Cm51.1, U18.7
ADC5_IN1P: Ci51.2, U18.6
ADC5_IN2M: Cm52.1, U18.9
ADC5_IN2P: Ci52.2, U18.8
ADC5_IN3M: Cm53.1, U18.11
ADC5_IN3P: Ci53.2, U18.10
ADC5_IN4M: Cm54.1, U18.13
ADC5_IN4P: Ci54.2, U18.12
ADC5_VREF: Cs55.1, U18.3
BOOT: C163.1, U13.4
BOOT0: Q2.3, R30.1, TP8.1, U6.166
BUCK_VCC: C166.1, U13.5
DBG_TX: TP12.1, U6.42
FB: R40.2, R41.1, U13.7
FLASH_DTR_N: Q2.1, R53.2, U32.13
FLASH_RTS_N: D11.1, U32.14
FLASH_RX: U6.94, U32.3
FLASH_TX: U6.95, U32.2
GND: C100.2, C101.2, C102.2, C103.2, C104.2, C105.2, C106.2, C107.2, C108.2, C109.2, C110.2, C111.2, C112.2, C113.2, C114.2, C115.2, C116.2, C117.2, C118.2, C119.2, C120.2, C121.2, C122.2, C123.2, C124.2, C125.2, C128.2, C129.2, C130.2, C131.2, C132.2, C133.2, C134.2, C135.2, C136.2, C137.2, C138.2, C139.2, C140.2, C141.2, C142.2, C143.2, C144.2, C145.2, C160.2, C161.2, C162.2, C164.2, C165.2, C166.2, C167.2, C180.2, C181.2, C182.2, C183.2, Cd1.2, Cd2.2, Cd3.2, Cd4.2, Cd5.2, Cd6.2, Cd7.2, Cd8.2, Cd9.2, Cd10.2, Cm11.2, Cm12.2, Cm13.2, Cm14.2, Cm21.2, Cm22.2, Cm23.2, Cm24.2, Cm31.2, Cm32.2, Cm33.2, Cm34.2, Cm41.2, Cm42.2, Cm43.2, Cm44.2, Cm51.2, Cm52.2, Cm53.2, Cm54.2, Cs11.2, Cs13.2, Cs15.2, Cs16.2, Cs18.2, Cs19.2, Cs21.2, Cs23.2, Cs25.2, Cs26.2, Cs28.2, Cs29.2, Cs31.2, Cs33.2, Cs35.2, Cs36.2, Cs38.2, Cs39.2, Cs41.2, Cs43.2, Cs45.2, Cs46.2, Cs48.2, Cs49.2, Cs51.2, Cs53.2, Cs55.2, Cs56.2, Cs58.2, Cs59.2, J1.A1, J1.A12, J1.B1, J1.B12, J1.SH, J2.2, Q1.2, R30.2, R32.2, R33.2, R35.2, R37.2, R38.2, R41.2, TP4.1, U6.14, U6.22, U6.37, U6.48, U6.61, U6.71, U6.90, U6.102, U6.113, U6.126, U6.135, U6.148, U6.158, U7.1, U7.2, U7.9, U7.33, U8.1, U9.2, U10.2, U11.2, U13.1, U13.6, U13.11, U14.4, U14.15, U14.16, U14.25, U15.4, U15.15, U15.16, U15.25, U16.4, U16.15, U16.16, U16.25, U17.4, U17.15, U17.16, U17.25, U18.4, U18.15, U18.16, U18.25, U21.4, U22.4, U23.4, U24.4, U25.4, U26.4, U27.4, U28.4, U29.4, U30.4, U31.25, U32.1, Y1.2, Y1.4, Y2.2, Y3.2, Y3.4
HUB_CH_DM: U31.9, U32.6
HUB_CH_DP: U31.10, U32.5
HUB_OVCUR_N: R52.2, U31.1
HUB_PHY_DM: U7.8, U31.11
HUB_PHY_DP: U7.7, U31.12
HUB_XI: U31.4, Y3.1
HUB_XO: U31.3, Y3.3
I2C2_SCL: R50.1, TP7.1, U6.17, U14.17, U15.17, U16.17, U17.17, U18.17
I2C2_SDA: R51.1, TP6.1, U6.16, U14.18, U15.18, U16.18, U17.18, U18.18
LED_A1: D1.2, R1.2
LED_A2: D2.2, R2.2
LED_A3: D3.2, R3.2
LED_A4: D4.2, R4.2
LED_A5: D5.2, R5.2
LED_A6: D6.2, R6.2
LED_A7: D7.2, R7.2
LED_A8: D8.2, R8.2
LED_A9: D9.2, R9.2
LED_A10: D10.2, R10.2
LED_GATE: R36.1, R38.1, U6.161
LED_GATE_Q: Q1.1, R36.2
LED_ROW: D1.1, D2.1, D3.1, D4.1, D5.1, D6.1, D7.1, D8.1, D9.1, D10.1, Q1.3
MID: C133.1, PD1A.1, PD1B.1, PD2A.1, PD2B.1, PD3A.1, PD3B.1, PD4A.1, PD4B.1, PD5A.1, PD5B.1, PD6A.1, PD6B.1, PD7A.1, PD7B.1, PD8A.1, PD8B.1, PD9A.1, PD9B.1, PD10A.1, PD10B.1, R42.2, U21.3, U21.5, U22.3, U22.5, U23.3, U23.5, U24.3, U24.5, U25.3, U25.5, U26.3, U26.5, U27.3, U27.5, U28.3, U28.5, U29.3, U29.5, U30.3, U30.5
MID_BUF: R42.1, U11.1, U11.4
MID_RAW: C114.1, R34.2, R35.1, U11.3
NRST: C135.1, D11.2, R31.1, TP3.1, U6.31
OSC_IN: C123.1, U6.29, Y1.1
OSC_OUT: C124.1, U6.30, Y1.3
PHY_1V8: C122.1, C137.1, C145.1, U7.15, U7.26
PHY_1V8A: C120.1, C136.1, U7.29
PHY_RBIAS: R37.1, U7.32
PHY_VBUS: R39.2, U7.4
PHY_XI: U7.28, Y2.3
SAI_FS: U6.3, U14.23, U15.23, U16.23, U17.23, U18.23
SAI_SCK: U6.4, U14.22, U15.22, U16.22, U17.22, U18.22
SAI_SD1: U6.5, U14.21
SAI_SD2: U6.2, U15.21
SAI_SD3: U6.40, U16.21
SAI_SD4: U6.175, U17.21
SAI_SD5: U6.143, U18.21
SHDNZ1: Cs19.1, Rs11.1, U14.14
SHDNZ2: Cs29.1, Rs21.1, U15.14
SHDNZ3: Cs39.1, Rs31.1, U16.14
SHDNZ4: Cs49.1, Rs41.1, U17.14
SHDNZ5: Cs59.1, Rs51.1, U18.14
SW: C163.2, L1.1, U13.3, U13.12
SWCLK: TP2.1, U6.137
SWDIO: TP1.1, U6.124
TIA_IN_1A: Cf1A.1, PD1A.2, Rf1A.1, U21.2
TIA_IN_1B: Cf1B.1, PD1B.2, Rf1B.1, U21.6
TIA_IN_2A: Cf2A.1, PD2A.2, Rf2A.1, U22.2
TIA_IN_2B: Cf2B.1, PD2B.2, Rf2B.1, U22.6
TIA_IN_3A: Cf3A.1, PD3A.2, Rf3A.1, U23.2
TIA_IN_3B: Cf3B.1, PD3B.2, Rf3B.1, U23.6
TIA_IN_4A: Cf4A.1, PD4A.2, Rf4A.1, U24.2
TIA_IN_4B: Cf4B.1, PD4B.2, Rf4B.1, U24.6
TIA_IN_5A: Cf5A.1, PD5A.2, Rf5A.1, U25.2
TIA_IN_5B: Cf5B.1, PD5B.2, Rf5B.1, U25.6
TIA_IN_6A: Cf6A.1, PD6A.2, Rf6A.1, U26.2
TIA_IN_6B: Cf6B.1, PD6B.2, Rf6B.1, U26.6
TIA_IN_7A: Cf7A.1, PD7A.2, Rf7A.1, U27.2
TIA_IN_7B: Cf7B.1, PD7B.2, Rf7B.1, U27.6
TIA_IN_8A: Cf8A.1, PD8A.2, Rf8A.1, U28.2
TIA_IN_8B: Cf8B.1, PD8B.2, Rf8B.1, U28.6
TIA_IN_9A: Cf9A.1, PD9A.2, Rf9A.1, U29.2
TIA_IN_9B: Cf9B.1, PD9B.2, Rf9B.1, U29.6
TIA_IN_10A: Cf10A.1, PD10A.2, Rf10A.1, U30.2
TIA_IN_10B: Cf10B.1, PD10B.2, Rf10B.1, U30.6
TIA_OUT_1A: Cf1A.2, Ci14.1, Rf1A.2, U21.1
TIA_OUT_1B: Cf1B.2, Ci13.1, Rf1B.2, U21.7
TIA_OUT_2A: Cf2A.2, Ci12.1, Rf2A.2, U22.1
TIA_OUT_2B: Cf2B.2, Ci11.1, Rf2B.2, U22.7
TIA_OUT_3A: Cf3A.2, Ci24.1, Rf3A.2, U23.1
TIA_OUT_3B: Cf3B.2, Ci23.1, Rf3B.2, U23.7
TIA_OUT_4A: Cf4A.2, Ci22.1, Rf4A.2, U24.1
TIA_OUT_4B: Cf4B.2, Ci21.1, Rf4B.2, U24.7
TIA_OUT_5A: Cf5A.2, Ci34.1, Rf5A.2, U25.1
TIA_OUT_5B: Cf5B.2, Ci33.1, Rf5B.2, U25.7
TIA_OUT_6A: Cf6A.2, Ci32.1, Rf6A.2, U26.1
TIA_OUT_6B: Cf6B.2, Ci31.1, Rf6B.2, U26.7
TIA_OUT_7A: Cf7A.2, Ci44.1, Rf7A.2, U27.1
TIA_OUT_7B: Cf7B.2, Ci43.1, Rf7B.2, U27.7
TIA_OUT_8A: Cf8A.2, Ci42.1, Rf8A.2, U28.1
TIA_OUT_8B: Cf8B.2, Ci41.1, Rf8B.2, U28.7
TIA_OUT_9A: Cf9A.2, Ci54.1, Rf9A.2, U29.1
TIA_OUT_9B: Cf9B.2, Ci53.1, Rf9B.2, U29.7
TIA_OUT_10A: Cf10A.2, Ci52.1, Rf10A.2, U30.1
TIA_OUT_10B: Cf10B.2, Ci51.1, Rf10B.2, U30.7
U8_VIN: C164.1, R54.2, U8.3
ULPI_CK: U6.51, U7.14
ULPI_D0: U6.47, U7.24
ULPI_D1: U6.56, U7.23
ULPI_D2: U6.57, U7.22
ULPI_D3: U6.79, U7.21
ULPI_D4: U6.80, U7.20
ULPI_D5: U6.92, U7.19
ULPI_D6: U6.93, U7.18
ULPI_D7: U6.163, U7.17
ULPI_DIR: U6.13, U7.12
ULPI_NXT: U6.45, U7.11
ULPI_STP: U6.32, U7.13
USB_CC1: J1.A5, R32.1
USB_CC2: J1.B5, R33.1
USB_DM: J1.A7, J1.B7, U10.3, U10.4, U31.14
USB_DP: J1.A6, J1.B6, U10.1, U10.6, U31.15
V5_DAMP: C134.1, R43.2
V5_PRE: C162.1, C167.1, FB1.1, L1.2, R1.1, R2.1, R3.1, R4.1, R5.1, R6.1, R7.1, R8.1, R9.1, R10.1, R40.1, R54.1
V24_IN: J2.1, R44.1, TP9.1
VBUS: C130.1, J1.A4, J1.A9, J1.B4, J1.B9, R39.1, U10.5
VCAP1: C112.1, U6.81
VCAP2: C113.1, U6.125

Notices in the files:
elec/output_board.py:
footprints' pad numbering (output_split's power half and the brain cite them from here).
